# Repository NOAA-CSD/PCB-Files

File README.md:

# PCB-Files
Printed Circuit Board projects that might be useful to others

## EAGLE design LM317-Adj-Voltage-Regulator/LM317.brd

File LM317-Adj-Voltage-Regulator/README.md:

Simple voltage regulator module with jumpers to select output voltage, dual input and dual output connectors

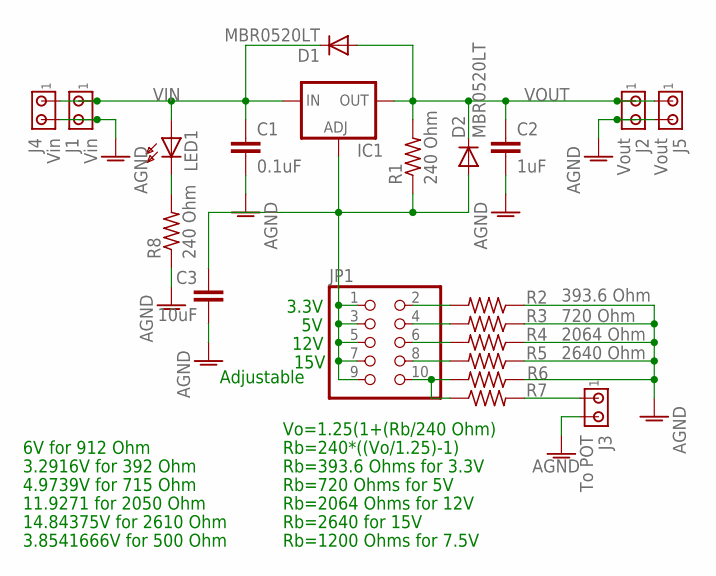
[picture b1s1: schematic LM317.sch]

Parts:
C1: 0.1uF; 0805_PANASONIC
C2: 1uF; 0805_PANASONIC
C3: 10uF; 0805_PANASONIC
D1, D2: MBR0520LT; SOD123
IC1: LM317TS; 317TS
J1, J4: Vin; 640456-2
J2, J5: Vout; 640456-2
J3: To POT; 640456-2
JP1: PINHD-2X5; 2X05
LED1: LED1206; M1206
R1, R8: 240 Ohm; 0805_MARISS
R2: 393.6 Ohm; 0805_MARISS
R3: 720 Ohm; 0805_MARISS
R4: 2064 Ohm; 0805_MARISS
R5: 2640 Ohm; 0805_MARISS
R6, R7: R_0805_MARISS; 0805_MARISS

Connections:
AGND: C1.2, C2.2, C3.2, J1.2, J2.2, J3.2, J4.2, J5.2, R2.1, R3.1, R4.1, R5.1, R6.1, R8.1
unnamed: J3.1, R7.2
unnamed: C3.1, D2.A, IC1.1 (ADJ), JP1.1, JP1.3, JP1.5, JP1.7, JP1.9, R1.1
unnamed: JP1.10, R6.2, R7.1
unnamed: JP1.8, R5.2
unnamed: JP1.6, R4.2
unnamed: JP1.4, R3.2
unnamed: LED1.2 (C), R8.2
unnamed: JP1.2, R2.2
VIN: C1.1, D1.C, IC1.3 (IN), J1.1, J4.1, LED1.1 (A)
VOUT: C2.1, D1.A, D2.C, IC1.2 (OUT), J2.1, J5.1, R1.2

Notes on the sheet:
Vo=1.25(1+(Rb/240 Ohm)
Rb=240*((Vo/1.25)-1)
Rb=393.6 Ohms for 3.3V
Rb=720 Ohms for 5V
Rb=2064 Ohms for 12V
Rb=2640 for 15V
Adjustable
3.3V
12V
15V
3.2916V for 392 Ohm
4.9739V for 715 Ohm
11.9271 for 2050 Ohm
14.84375V for 2610 Ohm
Rb=1200 Ohms for 7.5V
3.8541666V for 500 Ohm
6V for 912 Ohm

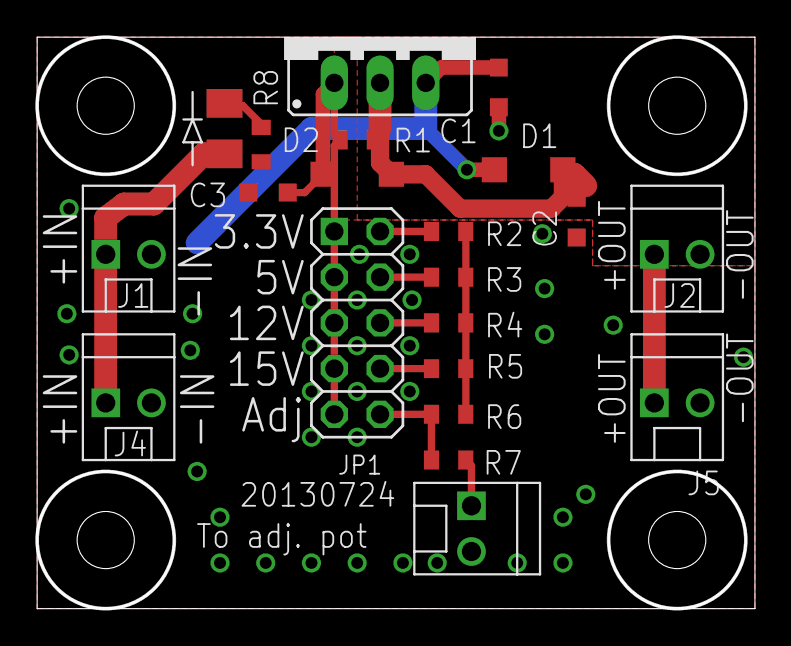
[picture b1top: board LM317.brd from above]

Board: 2 copper layers, 39.8 x 31.8 mm, 25 parts (0 on the bottom side), 11 nets.

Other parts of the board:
U$1, U$2, U$3, U$4: 440

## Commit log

2017-09-15 Pcb files edits (#1)
    * Add files via upload
    * Create README.md
    * Add files via upload
    * Delete LM317.brd
    * Delete LM317.sch
